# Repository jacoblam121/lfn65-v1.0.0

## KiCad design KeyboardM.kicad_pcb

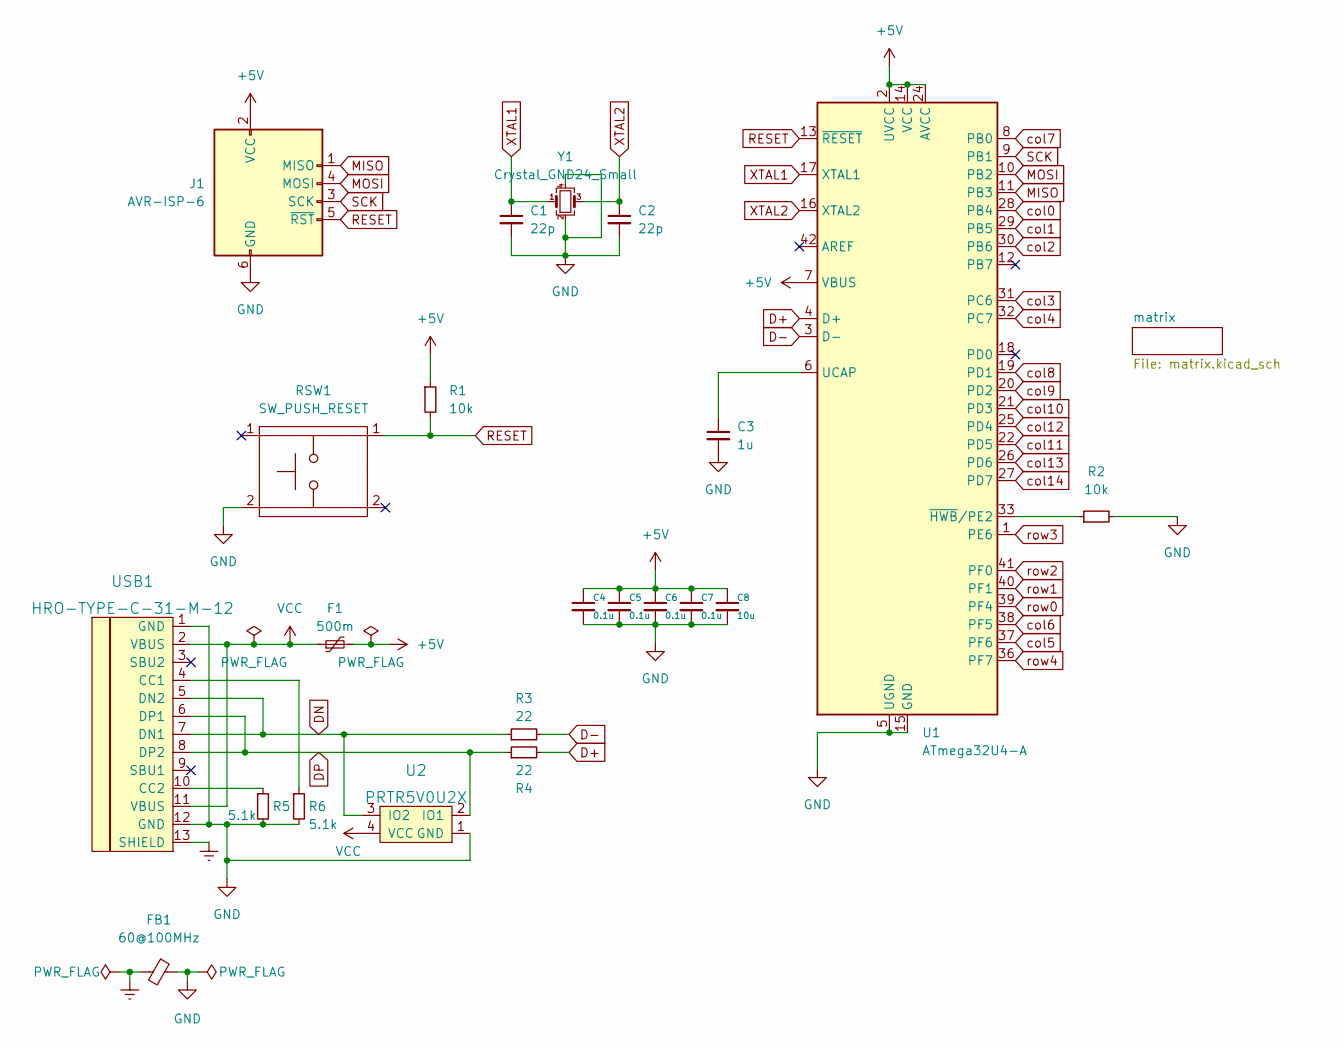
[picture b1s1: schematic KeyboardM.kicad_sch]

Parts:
C1, C2: 22p; C_0805_2012Metric_Pad1.18x1.45mm_HandSolder
C3: 1u; C_0805_2012Metric_Pad1.18x1.45mm_HandSolder
C4, C5, C6, C7: 0.1u; C_0805_2012Metric_Pad1.18x1.45mm_HandSolder
C8: 10u; C_0805_2012Metric_Pad1.18x1.45mm_HandSolder
F1: 500m; Fuse_1206_3216Metric_Pad1.42x1.75mm_HandSolder
FB1: 60@100MHz; L_0805_2012Metric_Pad1.15x1.40mm_HandSolder
J1: AVR-ISP-6; Reset_Pretty-Mask
R1, R2: 10k; R_0805_2012Metric_Pad1.20x1.40mm_HandSolder
R3, R4: 22; R_0805_2012Metric_Pad1.20x1.40mm_HandSolder
R5, R6: 5.1k; R_0805_2012Metric_Pad1.20x1.40mm_HandSolder
RSW1: SW_PUSH_RESET; SW_SPST_SKQG_WithStem
U1: ATmega32U4-A; TQFP-44_10x10mm_P0.8mm
U2: PRTR5V0U2X; SOT143B
USB1: HRO-TYPE-C-31-M-12; HRO-TYPE-C-31-M-12-HandSoldering
Y1: Crystal_GND24_Small; Crystal_SMD_3225-4Pin_3.2x2.5mm_HandSoldering

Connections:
+5V: C4.1, C5.1, C6.1, C7.1, C8.1, F1.2, J1.2 (VCC), R1.1, U1.2 (UVCC), U1.7 (VBUS), U1.14 (VCC), U1.24 (AVCC), U1.34 (VCC), U1.44 (AVCC)
D+: R4.2, U1.4 (D+)
D-: R3.2, U1.3 (D-)
DN: R3.1, U2.3 (IO2), USB1.5 (DN2), USB1.7 (DN1)
DP: R4.1, U2.2 (IO1), USB1.6 (DP1), USB1.8 (DP2)
Earth: FB1.2, USB1.13 (SHIELD)
GND: C1.2, C2.2, C3.2, C4.2, C5.2, C6.2, C7.2, C8.2, FB1.1, J1.6 (GND), R2.2, R5.2, R6.2, RSW1.2, U1.5 (UGND), U1.15 (GND), U1.23 (GND), U1.35 (GND), U1.43 (GND), U2.1 (GND), USB1.1 (GND), USB1.12 (GND), Y1.2, Y1.4
MISO: J1.1 (MISO), U1.11 (PB3)
MOSI: J1.4 (MOSI), U1.10 (PB2)
unnamed: C3.1, U1.6 (UCAP)
unnamed: R2.1, U1.33 (~HWB/PE2)
unnamed: R5.1, USB1.10 (CC2)
unnamed: R6.1, USB1.4 (CC1)
RESET: J1.5 (~RST), R1.2, RSW1.1, U1.13 (~RESET)
SCK: J1.3 (SCK), U1.9 (PB1)
VCC: F1.1, U2.4 (VCC), USB1.2 (VBUS), USB1.11 (VBUS)
XTAL1: C1.1, U1.17 (XTAL1), Y1.1
XTAL2: C2.1, U1.16 (XTAL2), Y1.3
col0: U1.28 (PB4); also elsewhere on the board
col1: U1.29 (PB5); also elsewhere on the board
col2: U1.30 (PB6); also elsewhere on the board
col3: U1.31 (PC6); also elsewhere on the board
col4: U1.32 (PC7); also elsewhere on the board
col5: U1.37 (PF6); also elsewhere on the board
col6: U1.38 (PF5); also elsewhere on the board
col7: U1.8 (PB0); also elsewhere on the board
col8: U1.19 (PD1); also elsewhere on the board
col9: U1.20 (PD2); also elsewhere on the board
col10: U1.21 (PD3); also elsewhere on the board
col11: U1.22 (PD5); also elsewhere on the board
col12: U1.25 (PD4); also elsewhere on the board
col13: U1.26 (PD6); also elsewhere on the board
col14: U1.27 (PD7); also elsewhere on the board
row0: U1.39 (PF4); also elsewhere on the board
row1: U1.40 (PF1); also elsewhere on the board
row2: U1.41 (PF0); also elsewhere on the board
row3: U1.1 (PE6); also elsewhere on the board
row4: U1.36 (PF7); also elsewhere on the board

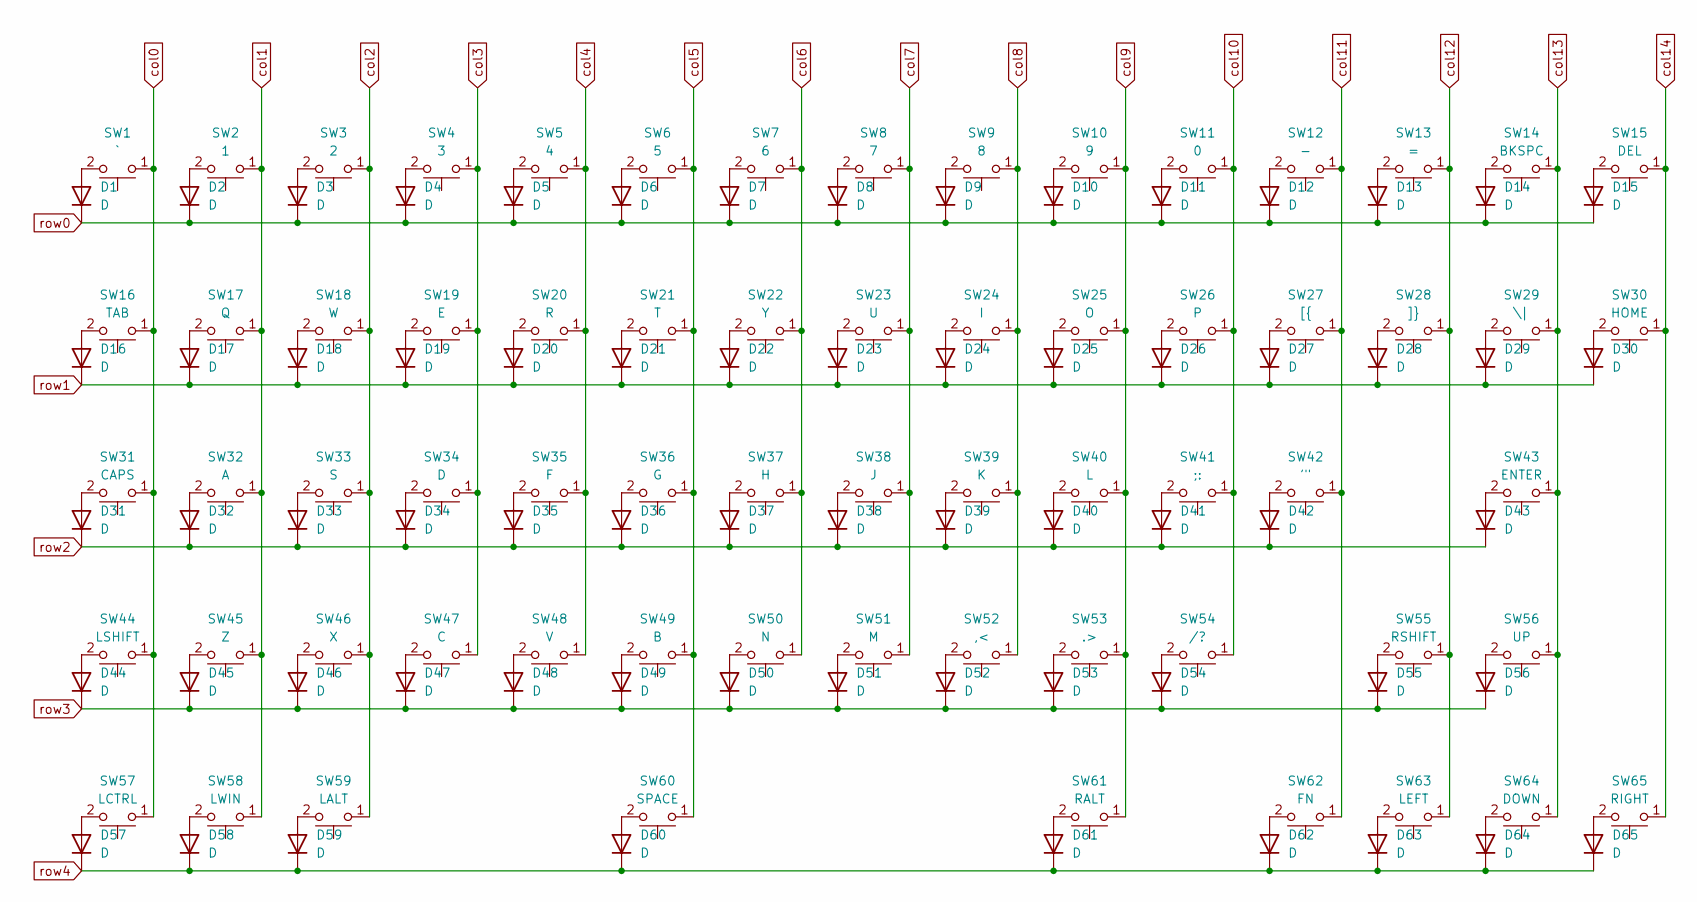
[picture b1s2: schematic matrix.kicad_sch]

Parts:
D1, D2, D3, D4, D5, D6, D7, D8, D9, D10, D11, D12, D13, D14, D15, D16, D17, D18, D19, D20, D21, D22, D23, D24, D25, D26, D27, D28, D29, D30, D31, D32, D33, D34, D35, D36, D37, D38, D39, D40, D41, D42, D43, D44, D45, D46, D47, D48, D49, D50, D51, D52, D53, D54, D55, D56, D57, D58, D59, D60, D61, D62, D63, D64, D65: D; D_SOD-123
SW1: `; MXOnly-1U
SW2: 1; MXOnly-1U
SW3: 2; MXOnly-1U
SW4: 3; MXOnly-1U
SW5: 4; MXOnly-1U
SW6: 5; MXOnly-1U
SW7: 6; MXOnly-1U
SW8: 7; MXOnly-1U
SW9: 8; MXOnly-1U
SW10: 9; MXOnly-1U
SW11: 0; MXOnly-1U
SW12: -; MXOnly-1U
SW13: =; MXOnly-1U
SW14: BKSPC; MXOnly-2U
SW15: DEL; MXOnly-1U
SW16: TAB; MXOnly-1.5U
SW17: Q; MXOnly-1U
SW18: W; MXOnly-1U
SW19: E; MXOnly-1U
SW20: R; MXOnly-1U
SW21: T; MXOnly-1U
SW22: Y; MXOnly-1U
SW23: U; MXOnly-1U
SW24: I; MXOnly-1U
SW25: O; MXOnly-1U
SW26: P; MXOnly-1U
SW27: [{; MXOnly-1U
SW28: ]}; MXOnly-1U
SW29: \|; MXOnly-1.5U
SW30: HOME; MXOnly-1U
SW31: CAPS; MXOnly-1.75U
SW32: A; MXOnly-1U
SW33: S; MXOnly-1U
SW34: D; MXOnly-1U
SW35: F; MXOnly-1U
SW36: G; MXOnly-1U
SW37: H; MXOnly-1U
SW38: J; MXOnly-1U
SW39: K; MXOnly-1U
SW40: L; MXOnly-1U
SW41: ;:; MXOnly-1U
SW42: '"; MXOnly-1U
SW43: ENTER; MXOnly-2.25U
SW44: LSHIFT; MXOnly-2.25U
SW45: Z; MXOnly-1U
SW46: X; MXOnly-1U
SW47: C; MXOnly-1U
SW48: V; MXOnly-1U
SW49: B; MXOnly-1U
SW50: N; MXOnly-1U
SW51: M; MXOnly-1U
SW52: ,<; MXOnly-1U
SW53: .>; MXOnly-1U
SW54: /?; MXOnly-1U
SW55: RSHIFT; MXOnly-1.75U
SW56: UP; MXOnly-1U
SW57: LCTRL; MXOnly-1.25U
SW58: LWIN; MXOnly-1.25U
SW59: LALT; MXOnly-1.25U
SW60: SPACE; MXOnly-6.25U
SW61: RALT; MXOnly-1.25U
SW62: FN; MXOnly-1.25U
SW63: LEFT; MXOnly-1U
SW64: DOWN; MXOnly-1U
SW65: RIGHT; MXOnly-1U

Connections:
unnamed: D1.2 (A), SW1.2
unnamed: D2.2 (A), SW2.2
unnamed: D3.2 (A), SW3.2
unnamed: D4.2 (A), SW4.2
unnamed: D5.2 (A), SW5.2
unnamed: D6.2 (A), SW6.2
unnamed: D7.2 (A), SW7.2
unnamed: D8.2 (A), SW8.2
unnamed: D9.2 (A), SW9.2
unnamed: D10.2 (A), SW10.2
unnamed: D11.2 (A), SW11.2
unnamed: D12.2 (A), SW12.2
unnamed: D13.2 (A), SW13.2
unnamed: D14.2 (A), SW14.2
unnamed: D15.2 (A), SW15.2
unnamed: D16.2 (A), SW16.2
unnamed: D17.2 (A), SW17.2
unnamed: D18.2 (A), SW18.2
unnamed: D19.2 (A), SW19.2
unnamed: D20.2 (A), SW20.2
unnamed: D21.2 (A), SW21.2
unnamed: D22.2 (A), SW22.2
unnamed: D23.2 (A), SW23.2
unnamed: D24.2 (A), SW24.2
unnamed: D25.2 (A), SW25.2
unnamed: D26.2 (A), SW26.2
unnamed: D27.2 (A), SW27.2
unnamed: D28.2 (A), SW28.2
unnamed: D29.2 (A), SW29.2
unnamed: D30.2 (A), SW30.2
unnamed: D31.2 (A), SW31.2
unnamed: D32.2 (A), SW32.2
unnamed: D33.2 (A), SW33.2
unnamed: D34.2 (A), SW34.2
unnamed: D35.2 (A), SW35.2
unnamed: D36.2 (A), SW36.2
unnamed: D37.2 (A), SW37.2
unnamed: D38.2 (A), SW38.2
unnamed: D39.2 (A), SW39.2
unnamed: D40.2 (A), SW40.2
unnamed: D41.2 (A), SW41.2
unnamed: D42.2 (A), SW42.2
unnamed: D43.2 (A), SW43.2
unnamed: D44.2 (A), SW44.2
unnamed: D45.2 (A), SW45.2
unnamed: D46.2 (A), SW46.2
unnamed: D47.2 (A), SW47.2
unnamed: D48.2 (A), SW48.2
unnamed: D49.2 (A), SW49.2
unnamed: D50.2 (A), SW50.2
unnamed: D51.2 (A), SW51.2
unnamed: D52.2 (A), SW52.2
unnamed: D53.2 (A), SW53.2
unnamed: D54.2 (A), SW54.2
unnamed: D55.2 (A), SW55.2
unnamed: D56.2 (A), SW56.2
unnamed: D57.2 (A), SW57.2
unnamed: D58.2 (A), SW58.2
unnamed: D59.2 (A), SW59.2
unnamed: D60.2 (A), SW60.2
unnamed: D61.2 (A), SW61.2
unnamed: D62.2 (A), SW62.2
unnamed: D63.2 (A), SW63.2
unnamed: D64.2 (A), SW64.2
unnamed: D65.2 (A), SW65.2
col0: SW1.1, SW16.1, SW31.1, SW44.1, SW57.1; also elsewhere on the board
col1: SW2.1, SW17.1, SW32.1, SW45.1, SW58.1; also elsewhere on the board
col2: SW3.1, SW18.1, SW33.1, SW46.1, SW59.1; also elsewhere on the board
col3: SW4.1, SW19.1, SW34.1, SW47.1; also elsewhere on the board
col4: SW5.1, SW20.1, SW35.1, SW48.1; also elsewhere on the board
col5: SW6.1, SW21.1, SW36.1, SW49.1, SW60.1; also elsewhere on the board
col6: SW7.1, SW22.1, SW37.1, SW50.1; also elsewhere on the board
col7: SW8.1, SW23.1, SW38.1, SW51.1; also elsewhere on the board
col8: SW9.1, SW24.1, SW39.1, SW52.1; also elsewhere on the board
col9: SW10.1, SW25.1, SW40.1, SW53.1, SW61.1; also elsewhere on the board
col10: SW11.1, SW26.1, SW41.1, SW54.1; also elsewhere on the board
col11: SW12.1, SW27.1, SW42.1, SW62.1; also elsewhere on the board
col12: SW13.1, SW28.1, SW55.1, SW63.1; also elsewhere on the board
col13: SW14.1, SW29.1, SW43.1, SW56.1, SW64.1; also elsewhere on the board
col14: SW15.1, SW30.1, SW65.1; also elsewhere on the board
row0: D1.1 (K), D2.1 (K), D3.1 (K), D4.1 (K), D5.1 (K), D6.1 (K), D7.1 (K), D8.1 (K), D9.1 (K), D10.1 (K), D11.1 (K), D12.1 (K), D13.1 (K), D14.1 (K), D15.1 (K); also elsewhere on the board
row1: D16.1 (K), D17.1 (K), D18.1 (K), D19.1 (K), D20.1 (K), D21.1 (K), D22.1 (K), D23.1 (K), D24.1 (K), D25.1 (K), D26.1 (K), D27.1 (K), D28.1 (K), D29.1 (K), D30.1 (K); also elsewhere on the board
row2: D31.1 (K), D32.1 (K), D33.1 (K), D34.1 (K), D35.1 (K), D36.1 (K), D37.1 (K), D38.1 (K), D39.1 (K), D40.1 (K), D41.1 (K), D42.1 (K), D43.1 (K); also elsewhere on the board
row3: D44.1 (K), D45.1 (K), D46.1 (K), D47.1 (K), D48.1 (K), D49.1 (K), D50.1 (K), D51.1 (K), D52.1 (K), D53.1 (K), D54.1 (K), D55.1 (K), D56.1 (K); also elsewhere on the board
row4: D57.1 (K), D58.1 (K), D59.1 (K), D60.1 (K), D61.1 (K), D62.1 (K), D63.1 (K), D64.1 (K), D65.1 (K); also elsewhere on the board

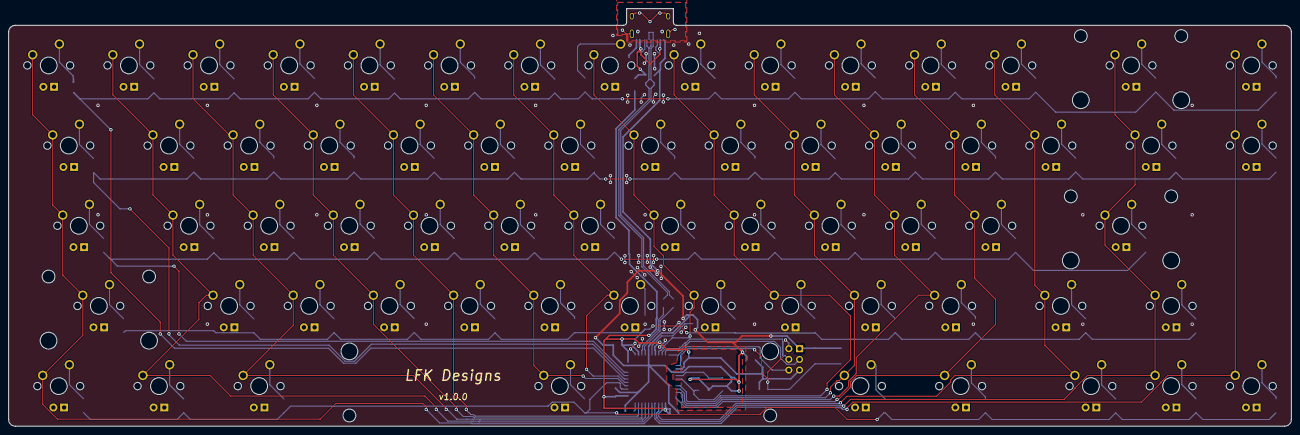
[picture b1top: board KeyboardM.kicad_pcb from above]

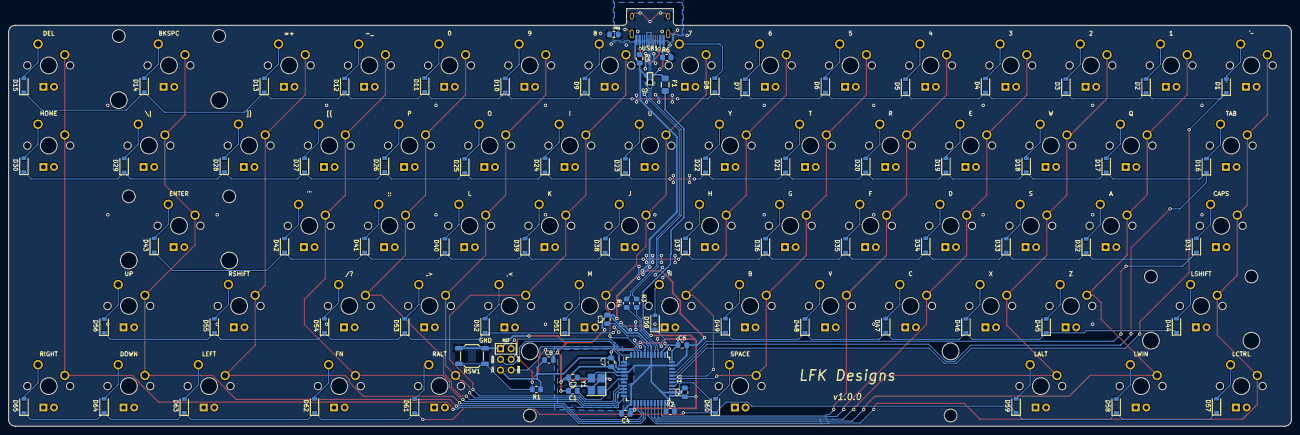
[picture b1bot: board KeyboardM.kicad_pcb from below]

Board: 2 copper layers, 304.8 x 99.2 mm, 152 parts (87 on the bottom side), 103 nets.

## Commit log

2023-01-29 Project Creation
2023-01-29 Rename
2023-02-02 Import Libraries
2023-02-02 Symbol Libraries
2023-02-02 MCU Setup Part 1
2023-02-02 Save
2023-02-04 ISP Header
2023-02-04 Schema Complete
2023-02-04 MX Only Footprint Library
2023-02-06 Switch Matrix
2023-02-06 Annotations/ERC Run
2023-02-06 Footprints Assigned
2023-02-06 PCB Updated
2023-02-06 Part 2 Complete
2023-02-09 Wiring
2023-02-18 Routing Complete
2023-02-19 v1.0.0
2023-02-19 Gerber + Drill/Map Files
2023-02-20 v1.0.1
